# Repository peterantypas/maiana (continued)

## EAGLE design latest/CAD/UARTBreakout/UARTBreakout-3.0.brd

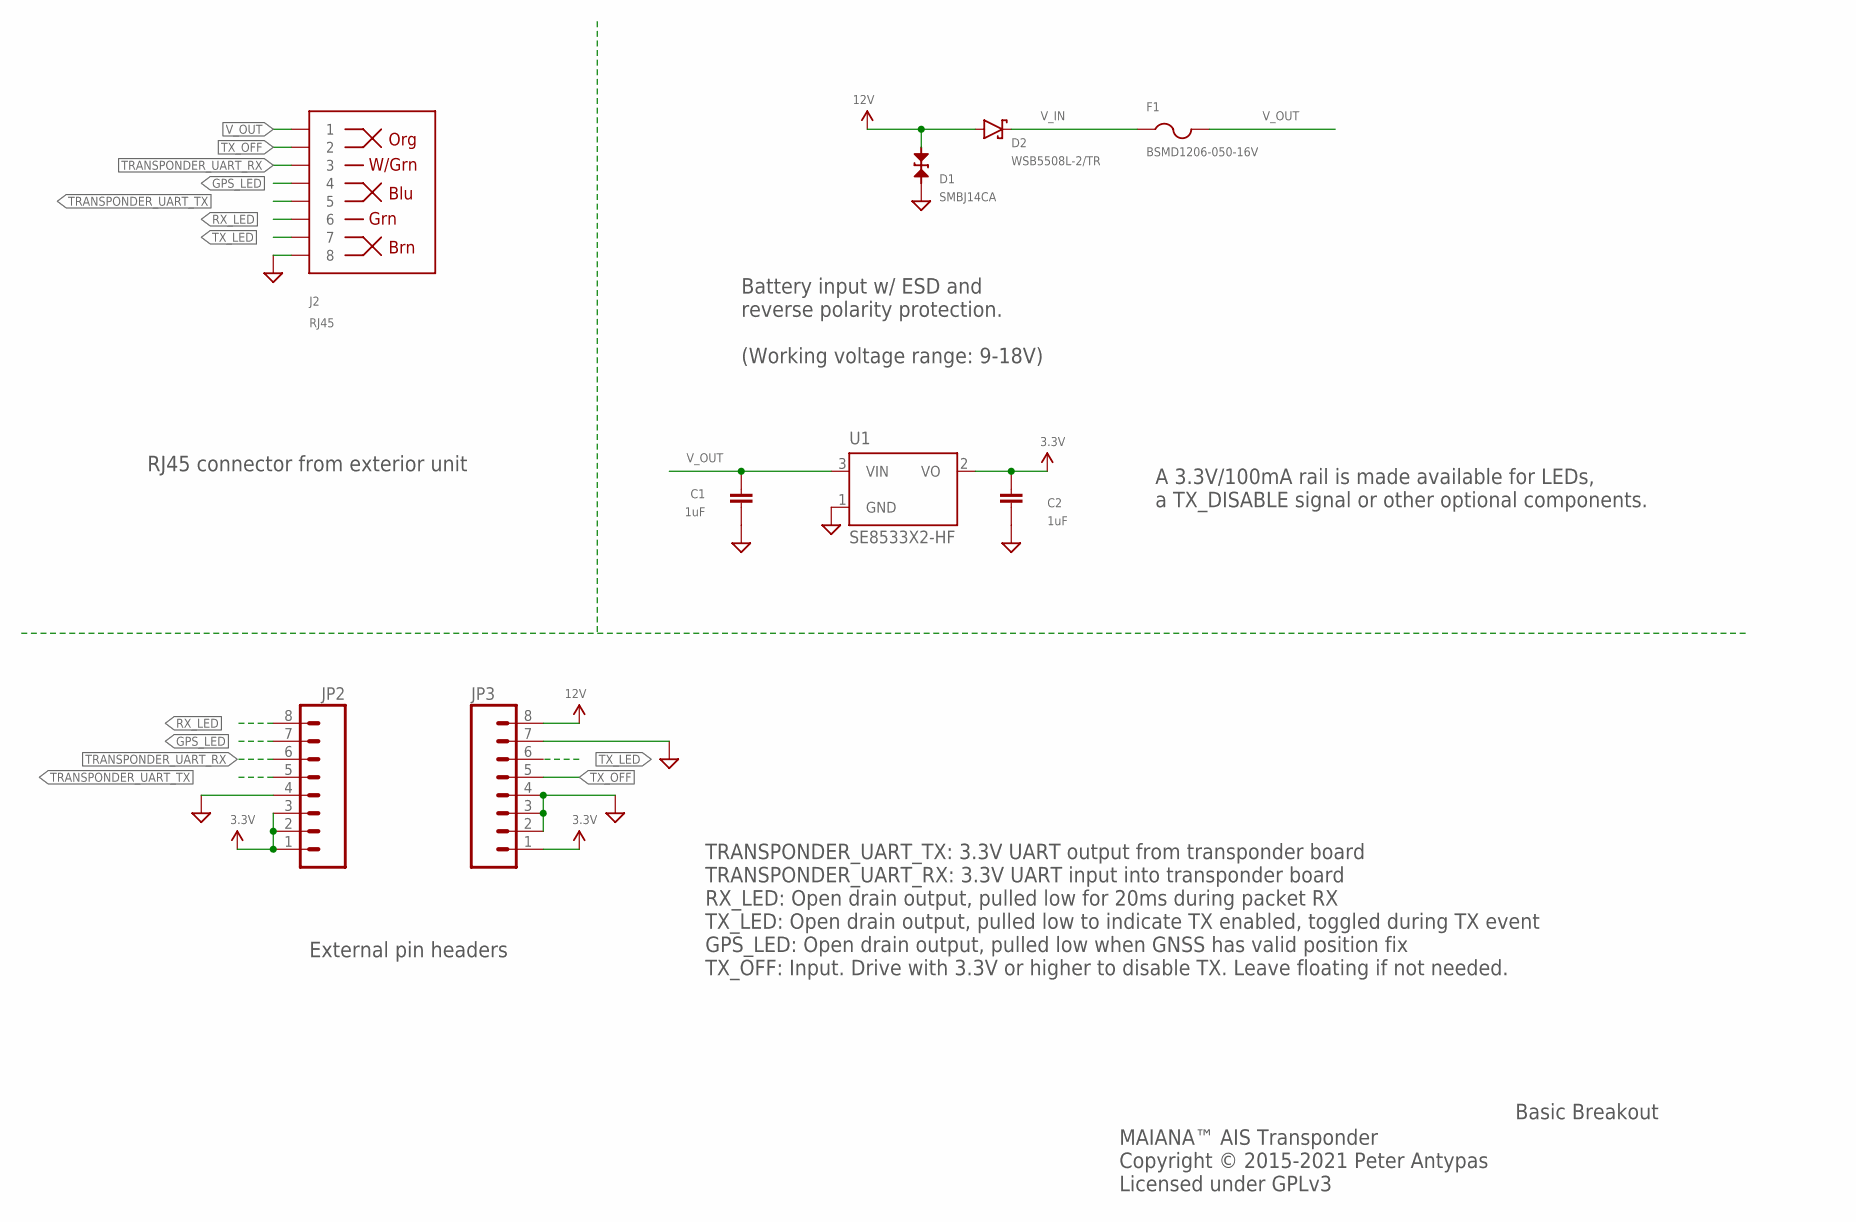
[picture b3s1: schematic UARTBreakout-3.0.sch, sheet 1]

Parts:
C1, C2: 1uF; 0603; PARTNO CC0603KRX5R8BB105
D1: SMBJ14CA; SMB-BIDIR; PARTNO SMBJ14CA
D2: WSB5508L-2/TR; SOD123; PARTNO WSB5508L-2/TR
F1: BSMD1206-050-16V; R1206; PARTNO BSMD1206-050-16V
J2: RJ45; RJ45-8; PARTNO 95501-2821
JP2, JP3: M08SILK_FEMALE_PTH; 1X08
U1: SE8533X2-HF; SOT23; PARTNO SE8533X2-HF

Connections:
3.3V: C2.P$1 (1), JP2.1, JP2.2, JP2.3, JP3.1, U1.2 (VO)
12V: D1.A, D2.A, JP3.8
GND: C1.P$2 (2), C2.P$2 (2), D1.C, J2.8, JP2.4, JP3.2, JP3.3, JP3.4, JP3.7, U1.1 (GND); also elsewhere on the board
GPS_LED: J2.4, JP2.7
RX_LED: J2.6, JP2.8
TRANSPONDER_UART_RX: J2.3, JP2.6; also elsewhere on the board
TRANSPONDER_UART_TX: J2.5, JP2.5; also elsewhere on the board
TX_LED: J2.7, JP3.6
TX_OFF: J2.2, JP3.5
V_IN: D2.C, F1.1
V_OUT: C1.P$1 (1), F1.2, J2.1, U1.3 (VIN)

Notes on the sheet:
MAIANA™ AIS Transponder Copyright © 2015-2021 Peter Antypas Licensed under GPLv3
Basic Breakout
Battery input w/ ESD and reverse polarity protection. (Working voltage range: 9-18V)
RJ45 connector from exterior unit
External pin headers
TRANSPONDER_UART_TX: 3.3V UART output from transponder board TRANSPONDER_UART_RX: 3.3V UART input into transponder board RX_LED: Open drain output, pulled low for 20ms during packet RX TX_LED: Open drain output, pulled low to indicate TX enabled, toggled during TX event GPS_LED: Open drain output, 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
A 3.3V/100mA rail is made available for LEDs, a TX_DISABLE signal or other optional components.

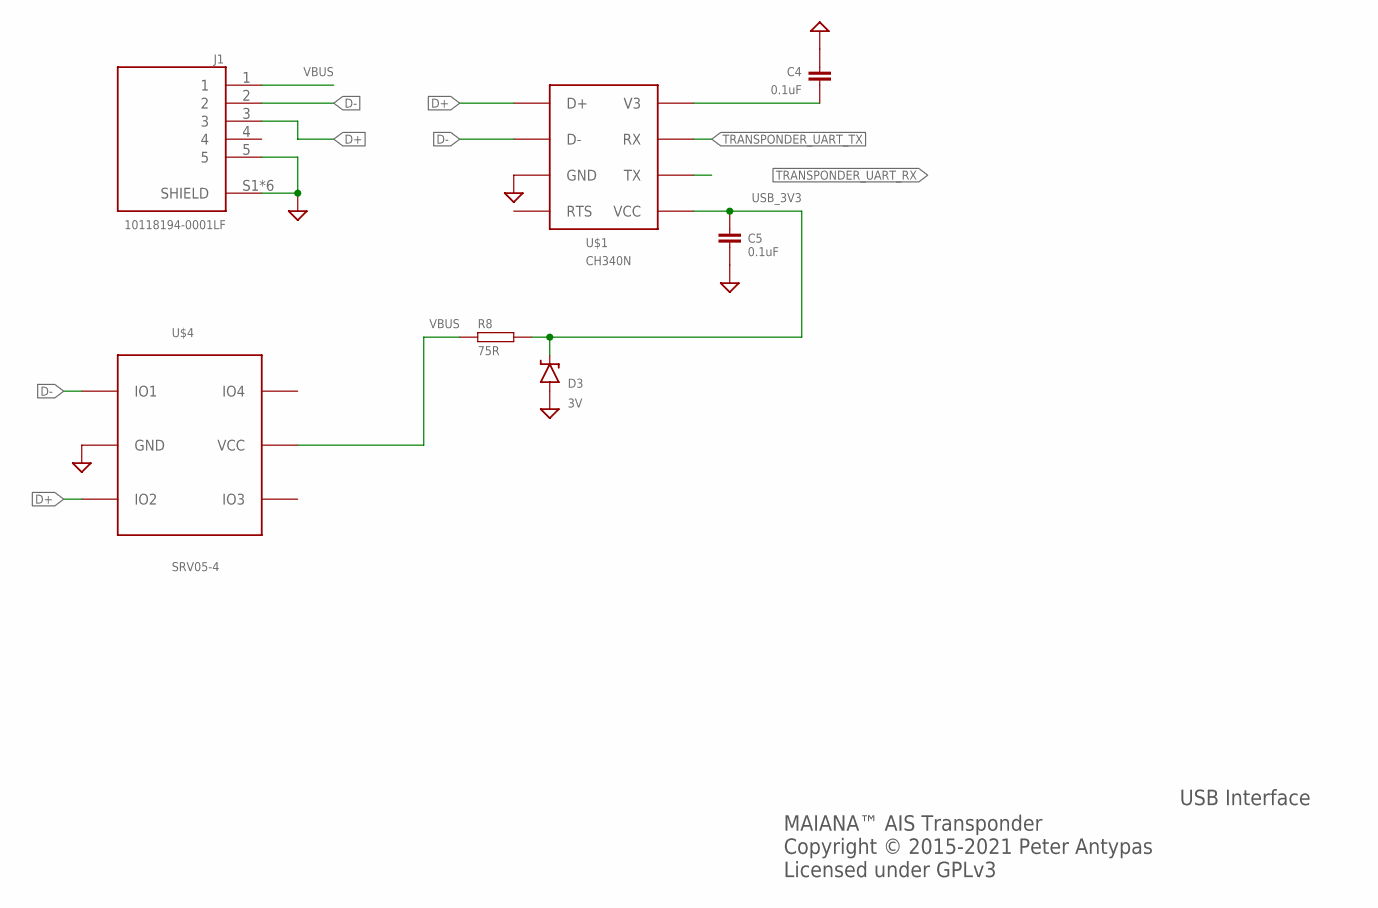
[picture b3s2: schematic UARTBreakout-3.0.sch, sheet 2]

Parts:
C4, C5: 0.1uF; 0603
D3: 3V; SOD-323
J1: 10118194-0001LF; AMPHENOL_10118194-0001LF
R8: 75R; 0603
U$1: CH340N; SOIC-8; PARTNO CH340N
U$4: SRV05-4; SOT23-6

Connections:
D+: J1.3, U$1.1 (D+), U$4.3 (IO2)
D-: J1.2, U$1.2 (D-), U$4.1 (IO1)
GND: C4.P$2 (2), C5.P$2 (2), D3.A, J1.5, J1.S1 (SHIELD), J1.S2 (SHIELD), J1.S3 (SHIELD), J1.S4 (SHIELD), J1.S5 (SHIELD), J1.S6 (SHIELD), U$1.3 (GND), U$4.2 (GND); also elsewhere on the board
unnamed: C4.P$1 (1), U$1.8 (V3)
TRANSPONDER_UART_RX: U$1.6 (TX); also elsewhere on the board
TRANSPONDER_UART_TX: U$1.7 (RX); also elsewhere on the board
USB_3V3: C5.P$1 (1), D3.C, R8.P$2, U$1.5 (VCC)
VBUS: J1.1, R8.P$1, U$4.5 (VCC)

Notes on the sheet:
MAIANA™ AIS Transponder Copyright © 2015-2021 Peter Antypas Licensed under GPLv3
USB Interface

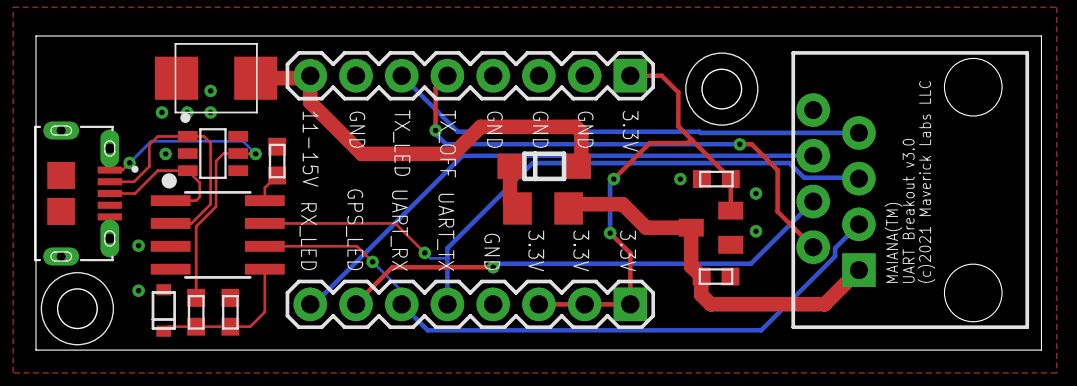
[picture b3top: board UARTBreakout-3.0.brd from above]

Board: 2 copper layers, 55.8 x 17.4 mm, 16 parts (0 on the bottom side), 16 nets.

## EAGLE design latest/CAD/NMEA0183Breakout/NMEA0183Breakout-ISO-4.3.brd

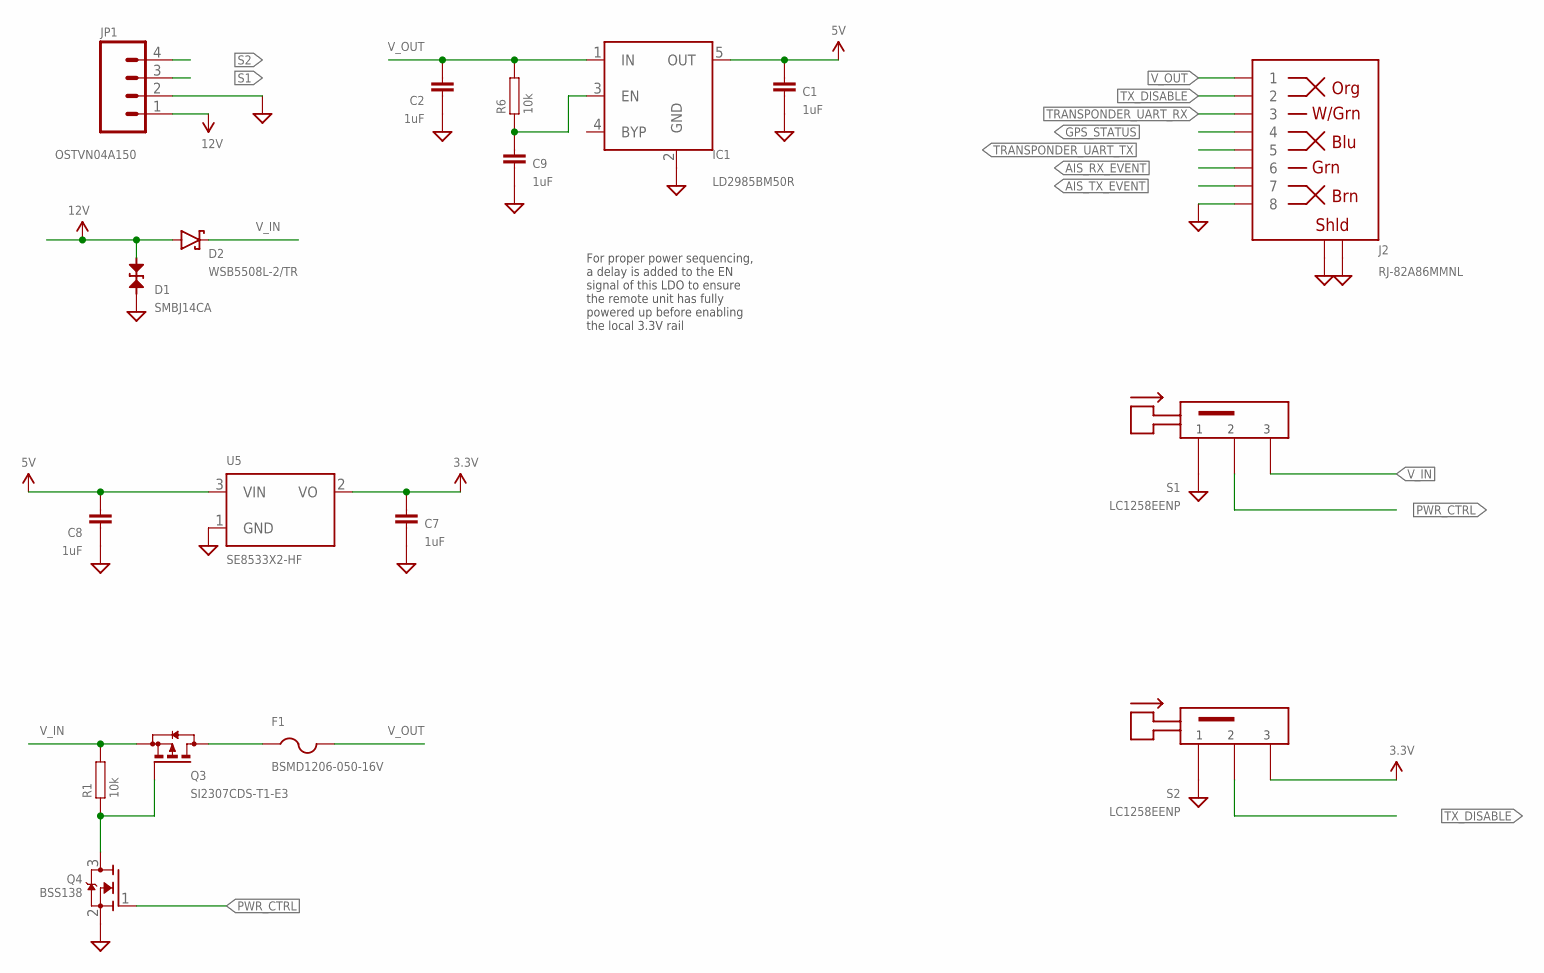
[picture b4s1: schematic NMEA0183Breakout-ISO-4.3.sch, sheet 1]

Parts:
C1, C2, C7, C8, C9: 1uF; 0603; PARTNO CC0603KRX5R8BB105
D1: SMBJ14CA; SMB-BIDIR; PARTNO SMBJ14CA
D2: WSB5508L-2/TR; SOD123; PARTNO WSB5508L-2/TR
F1: BSMD1206-050-16V; R1206; PARTNO BSMD1206-050-16V
IC1: LD2985BM50R; SOT23-5; PARTNO LD2985BM50R
J2: RJ-82A86MMNL
JP1: OSTVN04A150; 1X04; PARTNO OSTVN04A150
Q3: SI2307CDS-T1-E3; SOT23; PARTNO SI2307CDS-T1-E3
Q4: BSS138; SOT23; PARTNO BSS138
R1, R6: 10k; 0603; PARTNO RC0603FR-0710KL
S1, S2: LC1258EENP; LC1258XXNP; PARTNO LC1258EENP
U5: SE8533X2-HF; SOT23; PARTNO SE8533X2-HF

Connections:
3.3V: C7.P$1 (1), S2.P$3 (3), U5.2 (VO); also elsewhere on the board
5V: C1.P$1 (1), C8.P$1 (1), IC1.5 (OUT), U5.3 (VIN); also elsewhere on the board
12V: D1.A, D2.A, JP1.1
AIS_RX_EVENT: J2.P$6 (6); also elsewhere on the board
AIS_TX_EVENT: J2.P$7 (7); also elsewhere on the board
GND: C1.P$2 (2), C2.P$2 (2), C7.P$2 (2), C8.P$2 (2), C9.P$2 (2), D1.C, IC1.2 (GND), J2.P$8 (8), J2.P$9 (SHLD), J2.P$10 (SHLD), J2.P$11 (SHLD), J2.P$12 (SHLD), JP1.2, Q4.2 (S), S1.P$1 (1), S2.P$1 (1), U5.1 (GND); also elsewhere on the board
GPS_STATUS: J2.P$4 (4); also elsewhere on the board
unnamed: C9.P$1 (1), IC1.3 (EN), R6.P$1
unnamed: Q3.1 (G), Q4.3 (D), R1.P$1
unnamed: F1.1, Q3.3 (D)
PWR_CTRL: Q4.1 (G), S1.P$2 (2)
S1: JP1.3; also elsewhere on the board
S2: JP1.4; also elsewhere on the board
TRANSPONDER_UART_RX: J2.P$3 (3); also elsewhere on the board
TRANSPONDER_UART_TX: J2.P$5 (5); also elsewhere on the board
TX_DISABLE: J2.P$2 (2), S2.P$2 (2)
V_IN: D2.C, Q3.2 (S), R1.P$2, S1.P$3 (3)
V_OUT: C2.P$1 (1), F1.2, IC1.1 (IN), J2.P$1 (1), R6.P$2

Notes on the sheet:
For proper power sequencing, a delay is added to the EN signal of this LDO to ensure the remote unit has fully powered up before enabling the local 3.3V rail

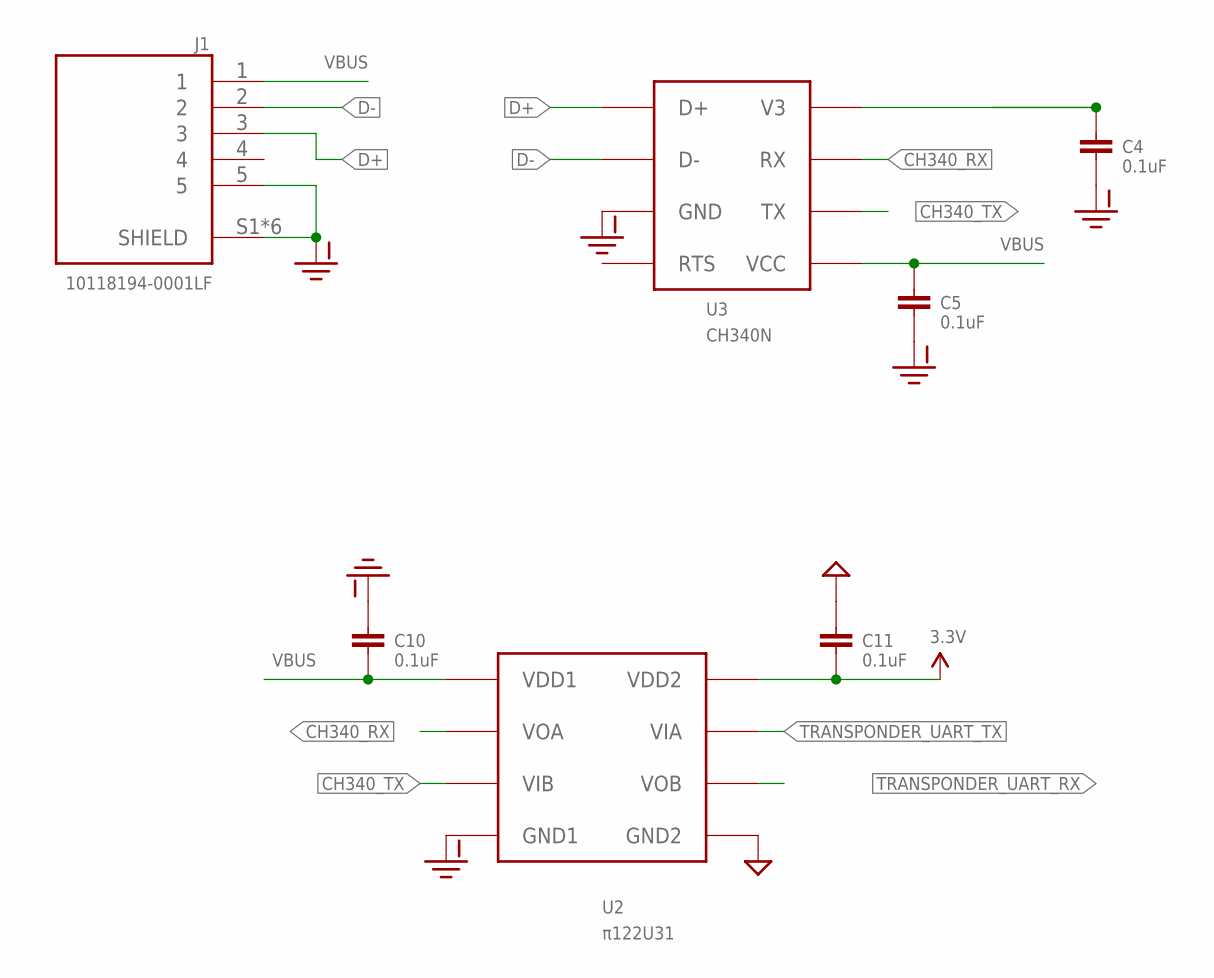
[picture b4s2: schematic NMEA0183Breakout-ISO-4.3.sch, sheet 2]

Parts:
C4, C5, C10, C11: 0.1uF; 0603; PARTNO 06035C104KAT2A
J1: 10118194-0001LF; AMPHENOL_10118194-0001LF; PARTNO 10118194-0001LF
U2: π122U31; SOIC8; PARTNO π122U31
U3: CH340N; SOIC-8; PARTNO CH340N

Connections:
3.3V: C11.P$2 (2), U2.8 (VDD2); also elsewhere on the board
CH340_RX: U2.2 (VOA), U3.7 (RX)
CH340_TX: U2.3 (VIB), U3.6 (TX)
D+: J1.3, U3.1 (D+)
D-: J1.2, U3.2 (D-)
GND: C11.P$1 (1), U2.5 (GND2); also elsewhere on the board
GND-ISO: C4.P$2 (2), C5.P$2 (2), C10.P$1 (1), J1.5, J1.S1 (SHIELD), J1.S2 (SHIELD), J1.S3 (SHIELD), J1.S4 (SHIELD), J1.S5 (SHIELD), J1.S6 (SHIELD), U2.4 (GND1), U3.3 (GND)
unnamed: C4.P$1 (1), U3.8 (V3)
TRANSPONDER_UART_RX: U2.6 (VOB); also elsewhere on the board
TRANSPONDER_UART_TX: U2.7 (VIA); also elsewhere on the board
VBUS: C5.P$1 (1), C10.P$2 (2), J1.1, U2.1 (VDD1), U3.5 (VCC)

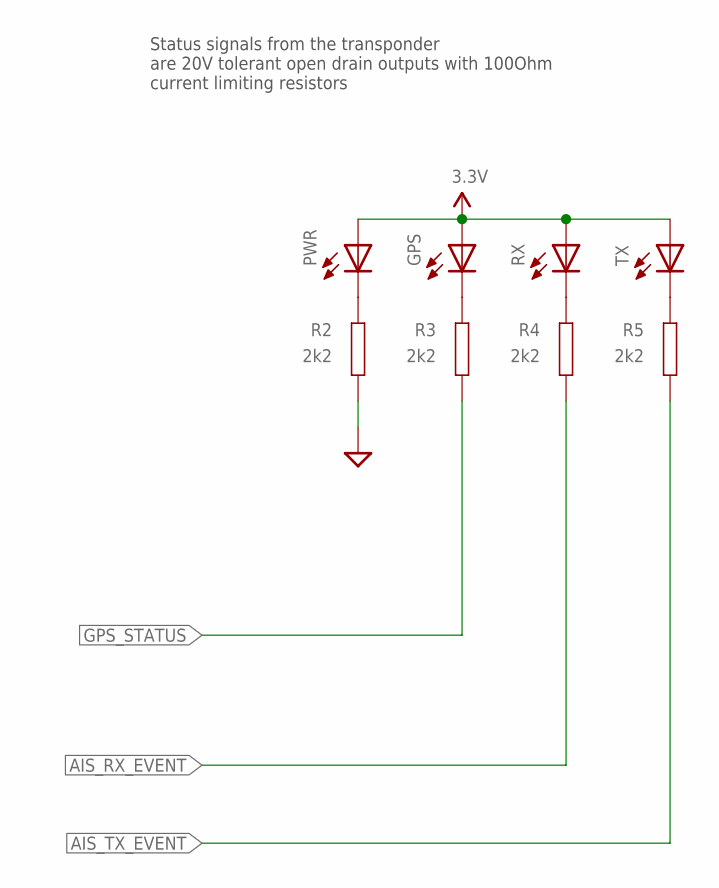
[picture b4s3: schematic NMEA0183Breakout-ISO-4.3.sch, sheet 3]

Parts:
GPS: LEDCHIPLED_1206; CHIPLED_1206; PARTNO TJ-S3216CL9T5ALC2G-A5
PWR: LEDCHIPLED_1206; CHIPLED_1206; PARTNO TJ-S3216CL9T5ALC2G-A5
R2, R3, R4, R5: 2k2; 0603; PARTNO CR0603-FX-2201ELF
RX: LEDCHIPLED_1206; CHIPLED_1206; PARTNO TJ-S3216CL9T5ALC2G-A5
TX: LEDCHIPLED_1206; CHIPLED_1206; PARTNO TJ-S3216CL9T5ALC2G-A5

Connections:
3.3V: GPS.A, PWR.A, RX.A, TX.A; also elsewhere on the board
AIS_RX_EVENT: R4.P$2; also elsewhere on the board
AIS_TX_EVENT: R5.P$2; also elsewhere on the board
GND: R2.P$2; also elsewhere on the board
GPS_STATUS: R3.P$2; also elsewhere on the board
unnamed: PWR.C, R2.P$1
unnamed: GPS.C, R3.P$1
unnamed: R4.P$1, RX.C
unnamed: R5.P$1, TX.C

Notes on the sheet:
Status signals from the transponder are 20V tolerant open drain outputs with 100Ohm current limiting resistors

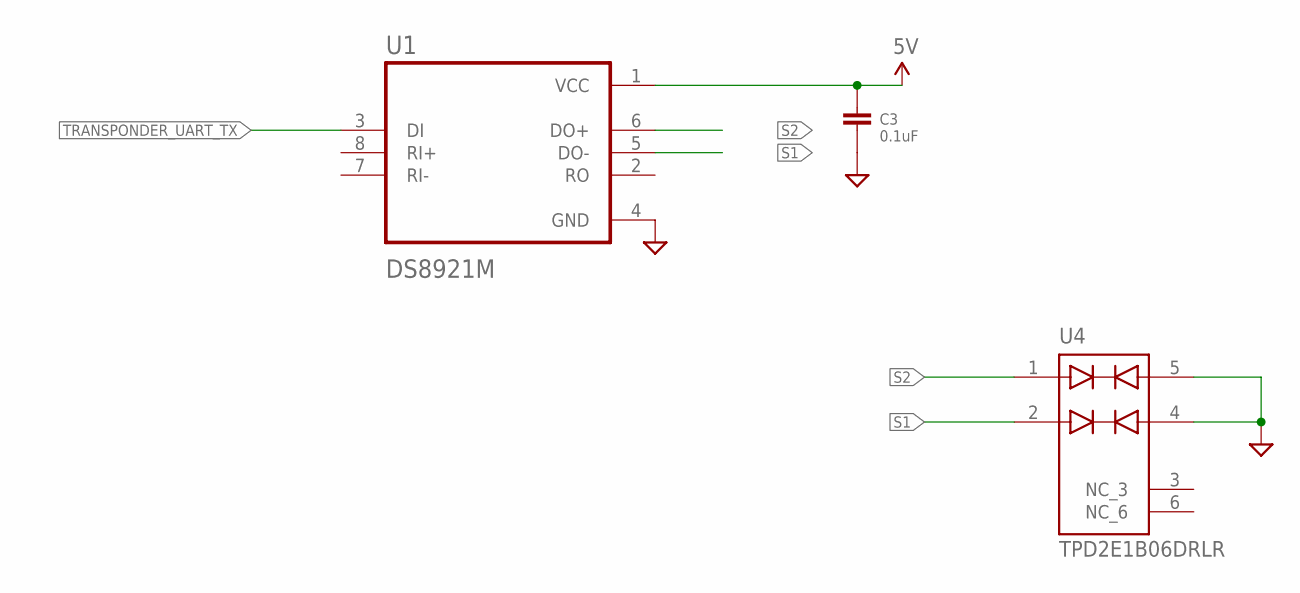
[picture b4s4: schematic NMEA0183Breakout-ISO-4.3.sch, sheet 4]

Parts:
C3: 0.1uF; 0603; PARTNO 06035C104KAT2A
U1: DS8921M; SOIC127P599X175-8N; PARTNO DS8921M
U4: TPD2E1B06DRLR; SOTFL50P160X60-6N; PARTNO TPD2E1B06DRLR

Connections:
5V: C3.P$1 (1), U1.1 (VCC); also elsewhere on the board
GND: C3.P$2 (2), U1.4 (GND), U4.4 (IOB2), U4.5 (IOA2); also elsewhere on the board
S1: U1.5 (DO-), U4.2 (IOB1); also elsewhere on the board
S2: U1.6 (DO+), U4.1 (IOA1); also elsewhere on the board
TRANSPONDER_UART_TX: U1.3 (DI); also elsewhere on the board

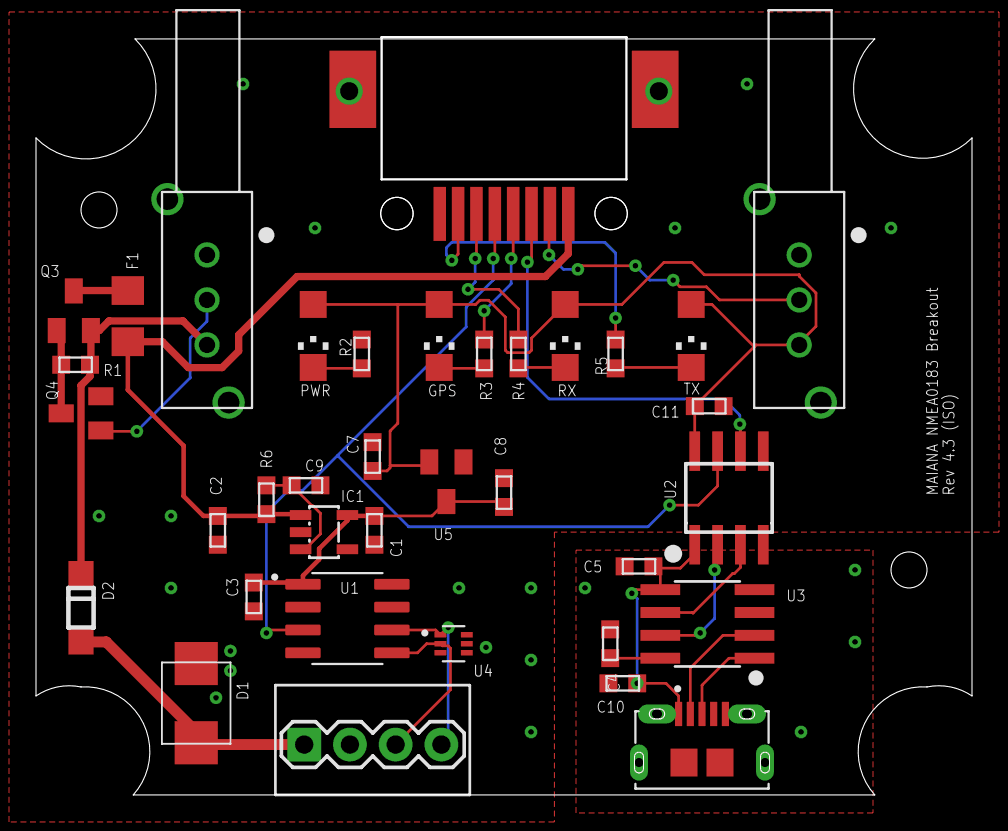
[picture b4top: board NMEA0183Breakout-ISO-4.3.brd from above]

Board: 2 copper layers, 51.9 x 42.0 mm, 36 parts (0 on the bottom side), 29 nets.

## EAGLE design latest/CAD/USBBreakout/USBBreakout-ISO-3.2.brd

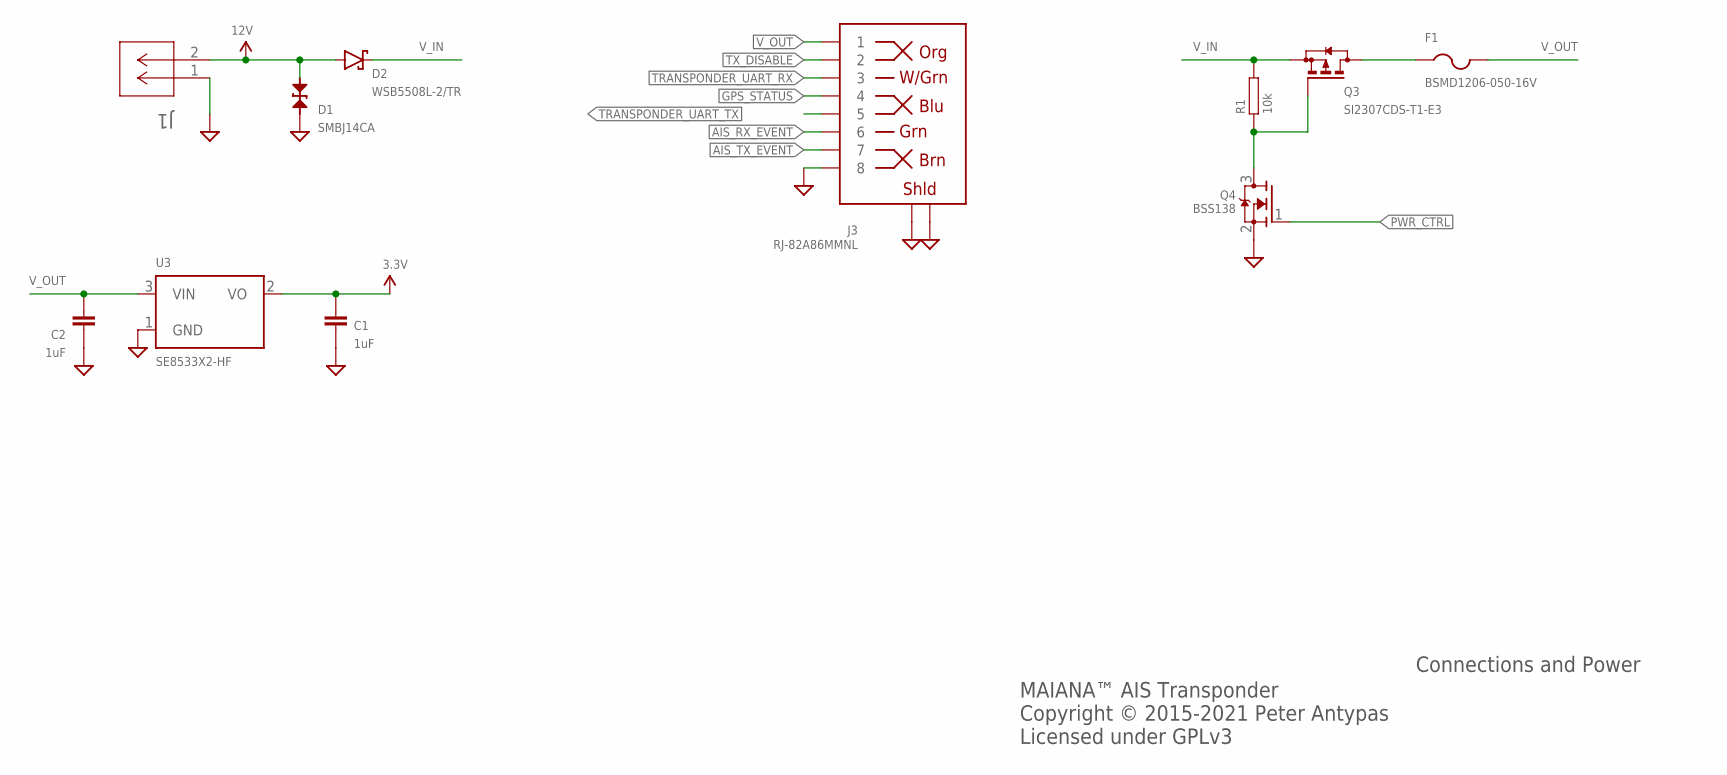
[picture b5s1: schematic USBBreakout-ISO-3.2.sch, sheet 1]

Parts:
C1, C2: 1uF; 0603; PARTNO CC0603KRX5R8BB105
D1: SMBJ14CA; SMB-BIDIR; PARTNO SMBJ14CA
D2: WSB5508L-2/TR; SOD123; PARTNO WSB5508L-2/TR
F1: BSMD1206-050-16V; R1206; PARTNO BSMD1206-050-16V
J1: OSTVN02A150; CONN_OSTVN02A150_OST; PARTNO OSTVN02A150
J3: RJ-82A86MMNL
Q3: SI2307CDS-T1-E3; SOT23; PARTNO SI2307CDS-T1-E3
Q4: BSS138; SOT23; PARTNO BSS138
R1: 10k; 0603; PARTNO RC0603FR-0710KL
U3: SE8533X2-HF; SOT23; PARTNO SE8533X2-HF

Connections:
3.3V: C1.P$1 (1), U3.2 (VO); also elsewhere on the board
12V: D1.A, D2.A, J1.2
AIS_RX_EVENT: J3.P$6 (6); also elsewhere on the board
AIS_TX_EVENT: J3.P$7 (7); also elsewhere on the board
GND: C1.P$2 (2), C2.P$2 (2), D1.C, J1.1, J3.P$8 (8), J3.P$9 (SHLD), J3.P$10 (SHLD), J3.P$11 (SHLD), J3.P$12 (SHLD), Q4.2 (S), U3.1 (GND); also elsewhere on the board
GPS_STATUS: J3.P$4 (4); also elsewhere on the board
unnamed: Q3.1 (G), Q4.3 (D), R1.P$1
unnamed: F1.1, Q3.3 (D)
PWR_CTRL: Q4.1 (G); also elsewhere on the board
TRANSPONDER_UART_RX: J3.P$3 (3); also elsewhere on the board
TRANSPONDER_UART_TX: J3.P$5 (5); also elsewhere on the board
TX_DISABLE: J3.P$2 (2); also elsewhere on the board
V_IN: D2.C, Q3.2 (S), R1.P$2; also elsewhere on the board
V_OUT: C2.P$1 (1), F1.2, J3.P$1 (1), U3.3 (VIN)

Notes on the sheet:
MAIANA™ AIS Transponder Copyright © 2015-2021 Peter Antypas Licensed under GPLv3
Connections and Power

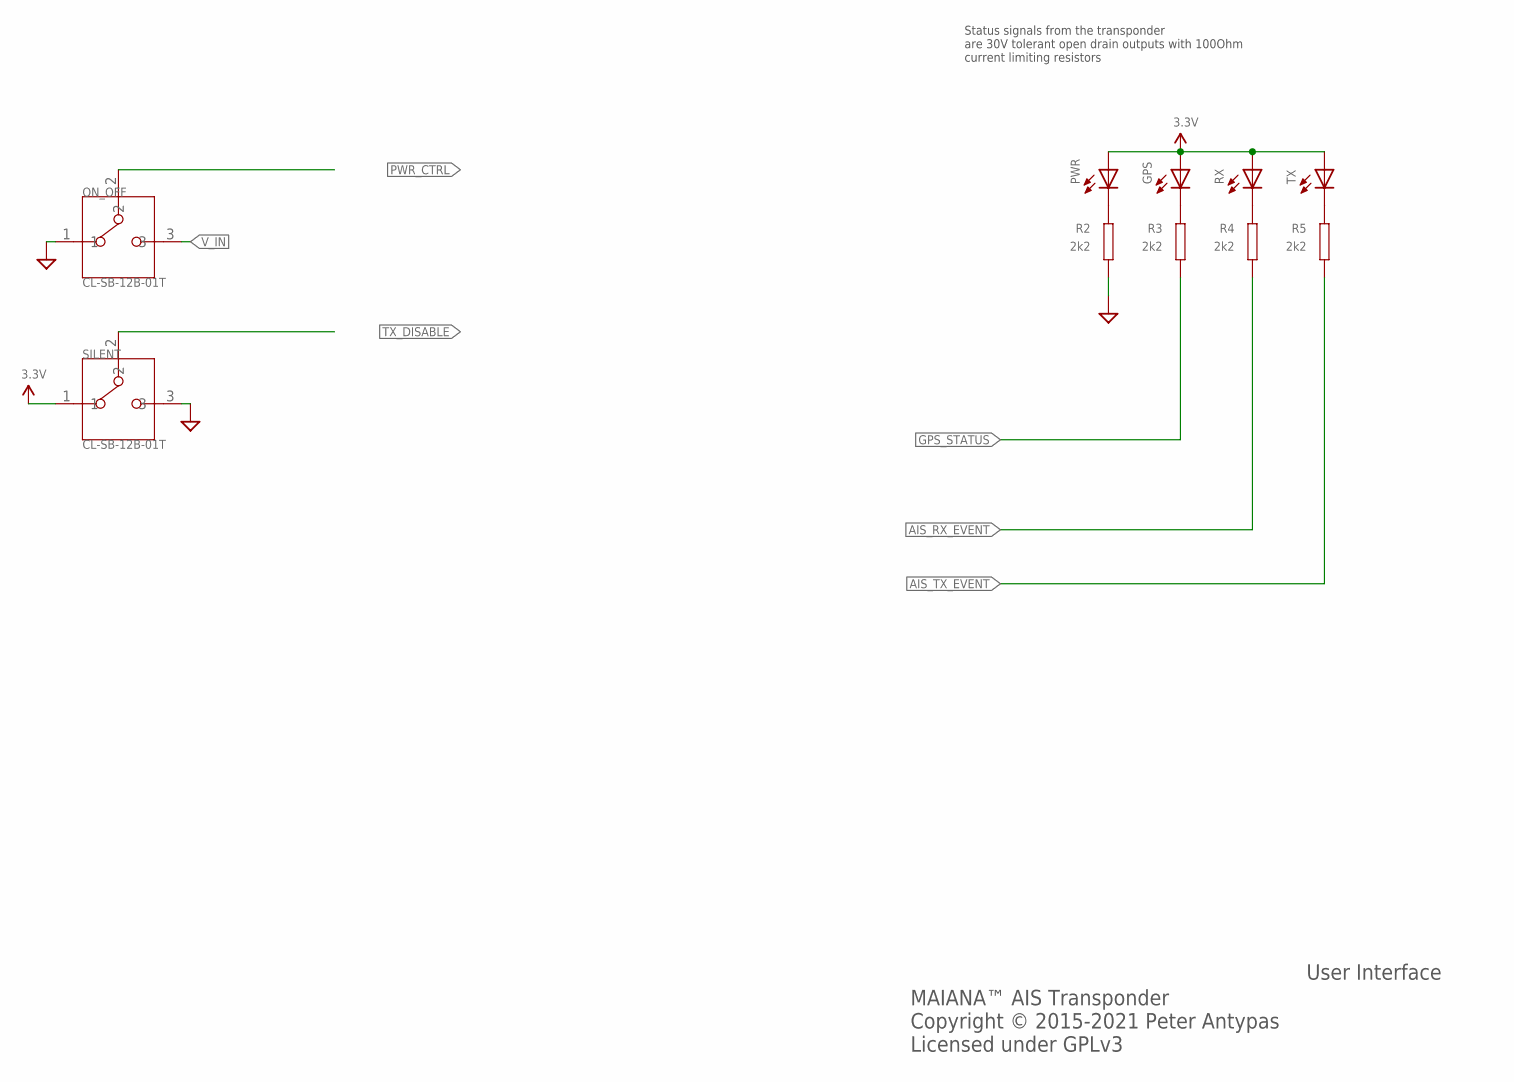
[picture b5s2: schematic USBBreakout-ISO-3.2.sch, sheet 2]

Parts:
GPS: LEDCHIPLED_1206; CHIPLED_1206; PARTNO TJ-S3216CL9T5ALC2G-A5
ON_OFF: CL-SB-12B-01T; CL-SB-12B; PARTNO CL-SB-12B-01T
PWR: LEDCHIPLED_1206; CHIPLED_1206; PARTNO TJ-S3216CL9T5ALC2G-A5
R2, R3, R4, R5: 2k2; 0603; PARTNO CR0603-FX-2201ELF
RX: LEDCHIPLED_1206; CHIPLED_1206; PARTNO TJ-S3216CL9T5ALC2G-A5
SILENT: CL-SB-12B-01T; CL-SB-12B; PARTNO CL-SB-12B-01T
TX: LEDCHIPLED_1206; CHIPLED_1206; PARTNO TJ-S3216CL9T5ALC2G-A5

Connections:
3.3V: GPS.A, PWR.A, RX.A, SILENT.1, TX.A; also elsewhere on the board
AIS_RX_EVENT: R4.P$2; also elsewhere on the board
AIS_TX_EVENT: R5.P$2; also elsewhere on the board
GND: ON_OFF.1, R2.P$2, SILENT.3; also elsewhere on the board
GPS_STATUS: R3.P$2; also elsewhere on the board
unnamed: PWR.C, R2.P$1
unnamed: GPS.C, R3.P$1
unnamed: R4.P$1, RX.C
unnamed: R5.P$1, TX.C
PWR_CTRL: ON_OFF.2; also elsewhere on the board
TX_DISABLE: SILENT.2; also elsewhere on the board
V_IN: ON_OFF.3; also elsewhere on the board

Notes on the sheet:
Status signals from the transponder are 30V tolerant open drain outputs with 100Ohm current limiting resistors
MAIANA™ AIS Transponder Copyright © 2015-2021 Peter Antypas Licensed under GPLv3
User Interface

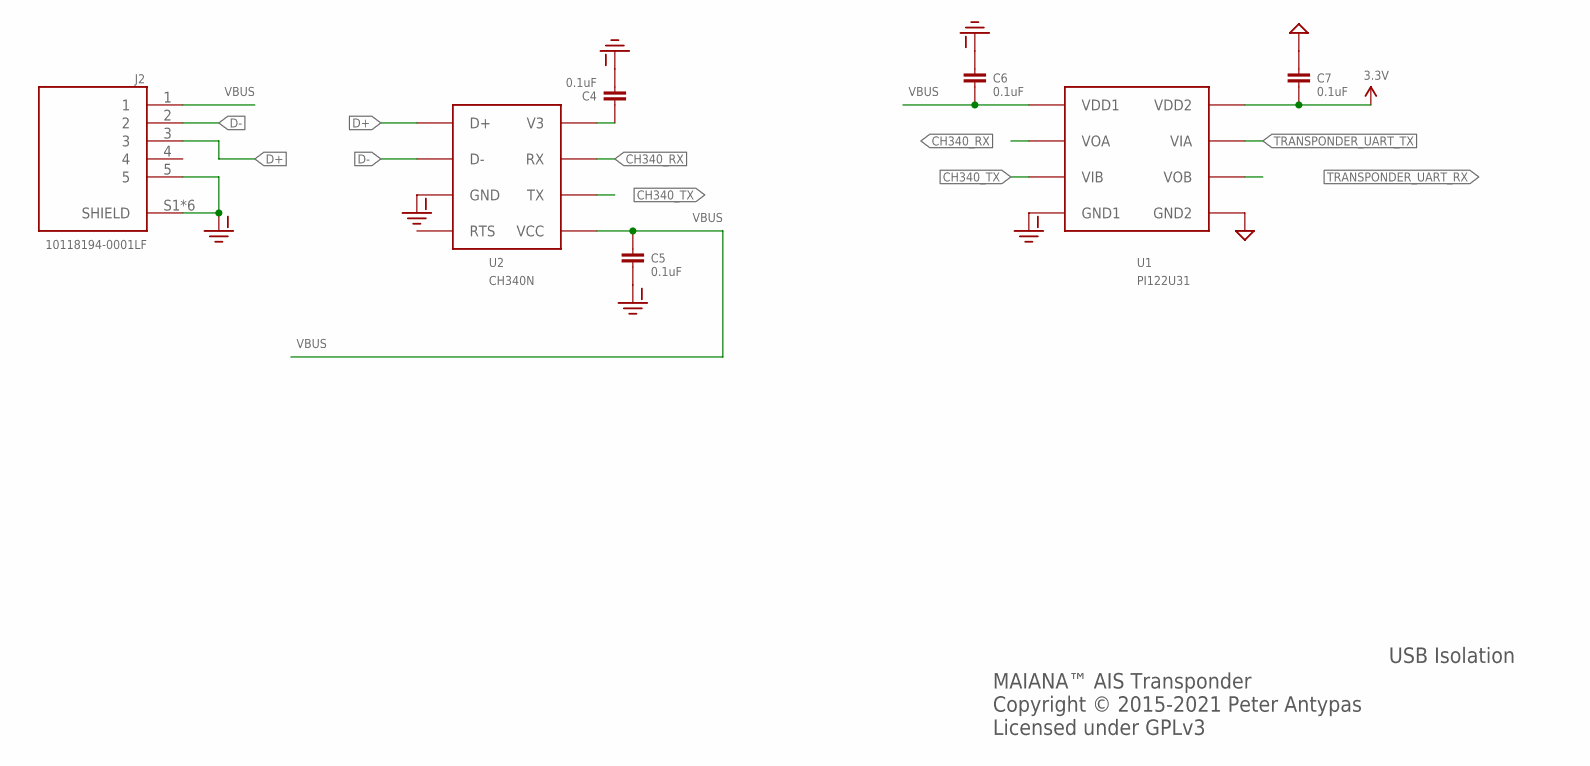
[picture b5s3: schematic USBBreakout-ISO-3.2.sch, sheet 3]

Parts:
C4, C5, C6, C7: 0.1uF; 0603; PARTNO 06035C104KAT2A
J2: 10118194-0001LF; AMPHENOL_10118194-0001LF; PARTNO 10118194-0001LF
U1: PI122U31; SOIC8; PARTNO Pi122U31
U2: CH340N; SOIC-8; PARTNO CH340N

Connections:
3.3V: C7.P$2 (2), U1.8 (VDD2); also elsewhere on the board
CH340_RX: U1.2 (VOA), U2.7 (RX)
CH340_TX: U1.3 (VIB), U2.6 (TX)
D+: J2.3, U2.1 (D+)
D-: J2.2, U2.2 (D-)
GND: C7.P$1 (1), U1.5 (GND2); also elsewhere on the board
GND-ISO: C4.P$2 (2), C5.P$2 (2), C6.P$1 (1), J2.5, J2.S1 (SHIELD), J2.S2 (SHIELD), J2.S3 (SHIELD), J2.S4 (SHIELD), J2.S5 (SHIELD), J2.S6 (SHIELD), U1.4 (GND1), U2.3 (GND)
unnamed: C4.P$1 (1), U2.8 (V3)
TRANSPONDER_UART_RX: U1.6 (VOB); also elsewhere on the board
TRANSPONDER_UART_TX: U1.7 (VIA); also elsewhere on the board
VBUS: C5.P$1 (1), C6.P$2 (2), J2.1, U1.1 (VDD1), U2.5 (VCC)

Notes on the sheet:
MAIANA™ AIS Transponder Copyright © 2015-2021 Peter Antypas Licensed under GPLv3
USB Isolation

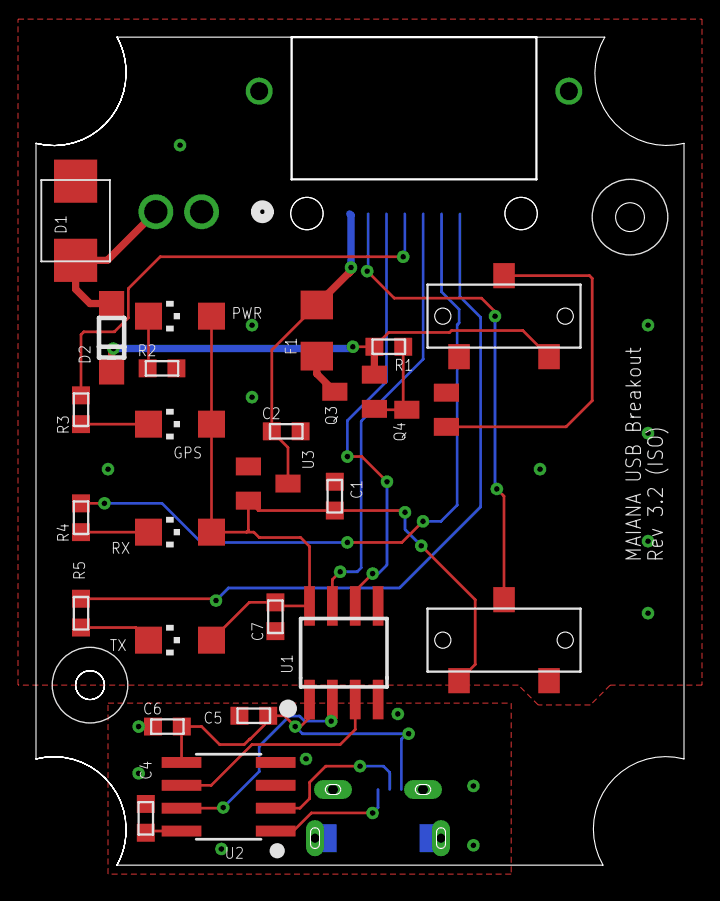
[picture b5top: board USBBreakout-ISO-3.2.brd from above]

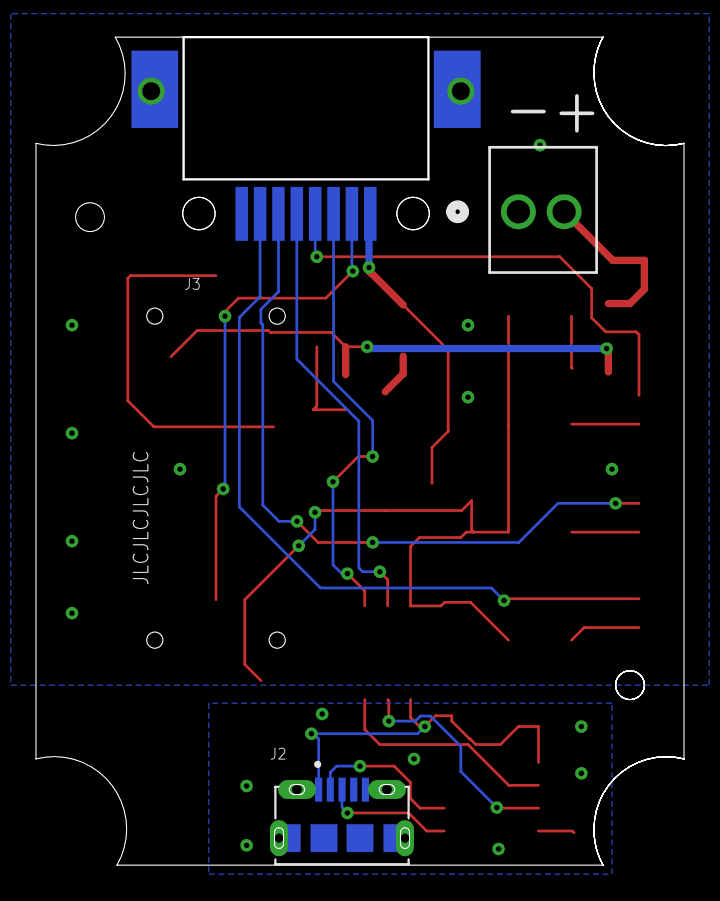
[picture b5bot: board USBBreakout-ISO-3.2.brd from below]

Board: 2 copper layers, 35.9 x 45.9 mm, 28 parts (3 on the bottom side), 25 nets.
